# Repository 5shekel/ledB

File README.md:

# ledB
old vs new

continued work from [eran](https://github.com/dodomarg/LED-B) kicad production version

this version is kicad with comments from Owe, thanks to Ralf 
and eveyone else at home-made who looked, made and tweaked this.

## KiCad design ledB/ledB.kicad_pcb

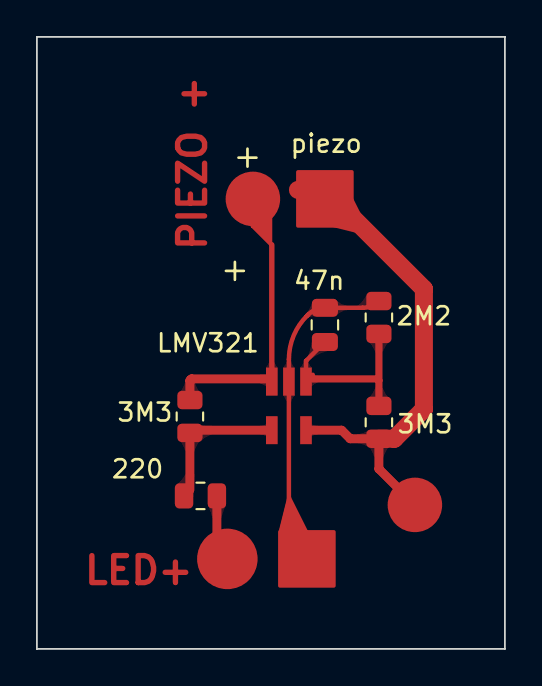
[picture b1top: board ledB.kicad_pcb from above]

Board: 2 copper layers, 26.0 x 34.0 mm, 6 parts (0 on the bottom side), 5 nets.

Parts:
2M2: 2M2; R_0805_2012Metric
3M3, 3M3#2: 3M3; R_0805_2012Metric
47n: 47n; C_0805_2012Metric
220: 220; R_0805_2012Metric
LMV321: LMV321; SOT-23-5_HandSoldering

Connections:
/piezo+: 3M3.2, LMV321.3 (-)
GND: 2M2.2, 47n.2, LMV321.2 (V-)
unnamed: 3M3.1, 220.1, LMV321.4
unnamed: 2M2.1, 3M3#2.2, 47n.1, LMV321.1 (+)
VCC: 3M3#2.1, LMV321.5 (V+)

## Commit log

2024-08-01 schema
2024-08-02 hmem-made2
2024-08-02 homemade2
2024-08-02 eran version
2024-08-02 new png
2024-08-02 baked
2024-09-19 sent to fab
2024-11-09 v2 based on ledman
2024-11-09 diy ledman
2024-11-09 rounded
2024-11-09 etch
2025-10-13 fit schema to wue site
